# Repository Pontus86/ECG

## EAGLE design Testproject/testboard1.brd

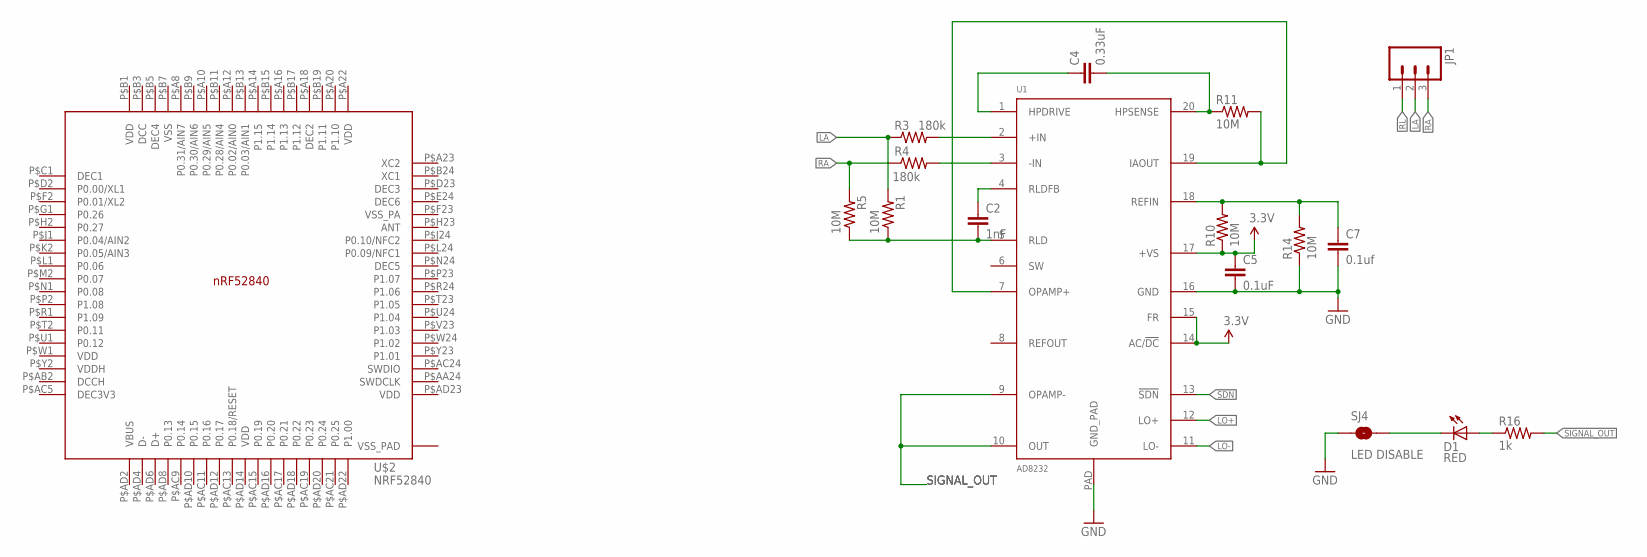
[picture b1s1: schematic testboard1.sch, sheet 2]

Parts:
C2: 1nF; 0603-CAP
C4: 0.33uF; 0805
C5: 0.1uF; 0603-CAP
C7: 0.1uf; 0603-CAP
D1: RED; LED-0603
JP1: M03PTH; 1X03
R1, R5, R10, R11, R14: 10M; 0603-RES
R3, R4: 180k; 0603-RES
R16: 1k; 0603-RES
SJ4: LED DISABLE; SJ_2S-TRACE
U1: AD8232; LFCSP_20
U$2: NRF52840; AQFN50P700X700X85_HS-74N

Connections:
3.3V: C5.1, R10.1, U1.14 (AC/!DC), U1.15 (FR), U1.17 (+VS)
DEC1: U$2.P$C1 (DEC1)
DEC4: U$2.P$B5 (DEC4)
GND: C5.2, C7.2, R14.1, SJ4.1, U1.16 (GND), U1.PAD (GND_PAD)
LA: JP1.2, R1.2, R3.1
LO+: U1.12 (LO+)
LO-: U1.11 (LO-)
unnamed: R3.2, U1.2 (+IN)
unnamed: R4.2, U1.3 (-IN)
unnamed: C4.2, R11.1, U1.20 (HPSENSE)
unnamed: C7.1, R10.2, R14.2, U1.18 (REFIN)
unnamed: D1.A, R16.1
unnamed: D1.C, SJ4.2
unnamed: C4.1, U1.1 (HPDRIVE)
unnamed: C2.1, U1.4 (RLDFB)
unnamed: C2.2, R1.1, R5.1, U1.5 (RLD)
RA: JP1.3, R4.1, R5.2
RL: JP1.1
SDN: U1.13 (!SDN)
SIGNAL_OUT: R11.2, R16.2, U1.7 (OPAMP+), U1.9 (OPAMP-), U1.10 (OUT), U1.19 (IAOUT)
VBUS: U$2.P$AD2 (VBUS)
VDD: U$2.P$A22 (VDD), U$2.P$AD14 (VDD), U$2.P$AD23 (VDD), U$2.P$B1 (VDD), U$2.P$W1 (VDD)
VDDH: U$2.P$Y2 (VDDH)
VSS: U$2.P$B7 (VSS)

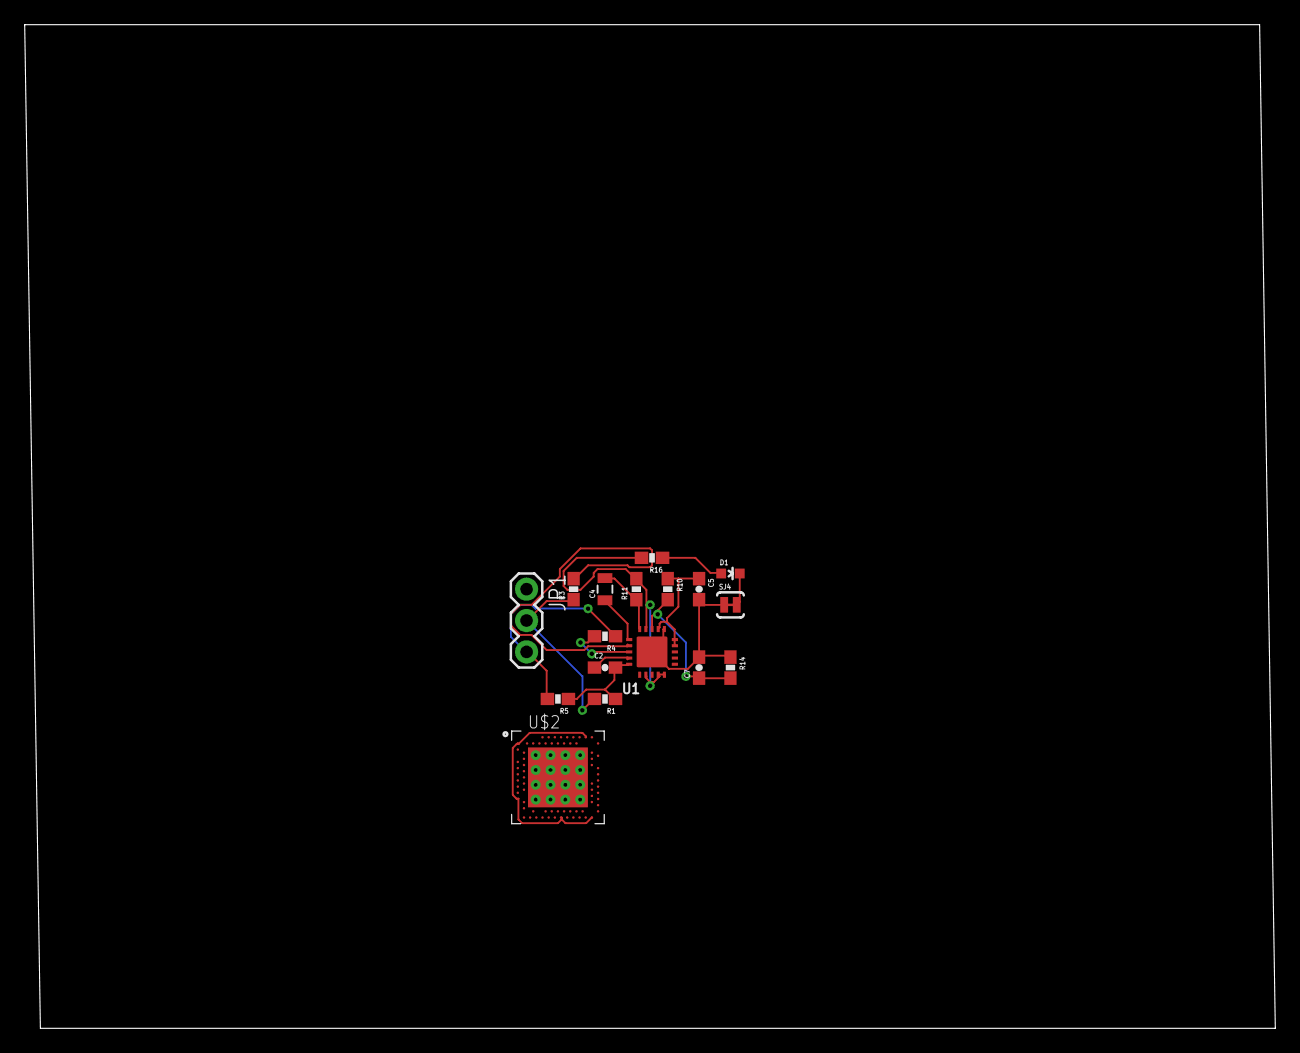
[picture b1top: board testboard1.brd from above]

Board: 2 copper layers, 101.3 x 81.3 mm, 17 parts (0 on the bottom side), 15 nets.

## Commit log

2019-01-20 Add project
    added AD8232 files and testproject files
2019-01-20 updated board design
    updated board design

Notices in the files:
parts and their libraries:
SparkFun-Passives: Licensing: CC v3.0 Share-Alike You are welcome to use this library for commercial purposes.
